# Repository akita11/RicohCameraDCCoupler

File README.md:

# Ricoh Camera DC Coupler

DC power supply coupler for Ricoh WG-10. Supply 7V or above to operate WG-10.

## Build

- fabricate PCB using "SMC-DCc10_gerber.zip" (original design using Eagle, PCB specs are shown in "SMC-DCc10_BOM.xlsx".), and divide into two sub-boards. (smaller one is outside WG-10 to attach external power cable, larger one is DC coupler attached in WG-10's battery area.)
- solder components listed in  "SMC-DCc10_BOM.xlsx".
- additional component: [FPC cable](https://www.digikey.jp/ja/products/detail/molex-llc/0151660079/3280961)

## Author

Junichi Akita (akita@ifdl.jp)

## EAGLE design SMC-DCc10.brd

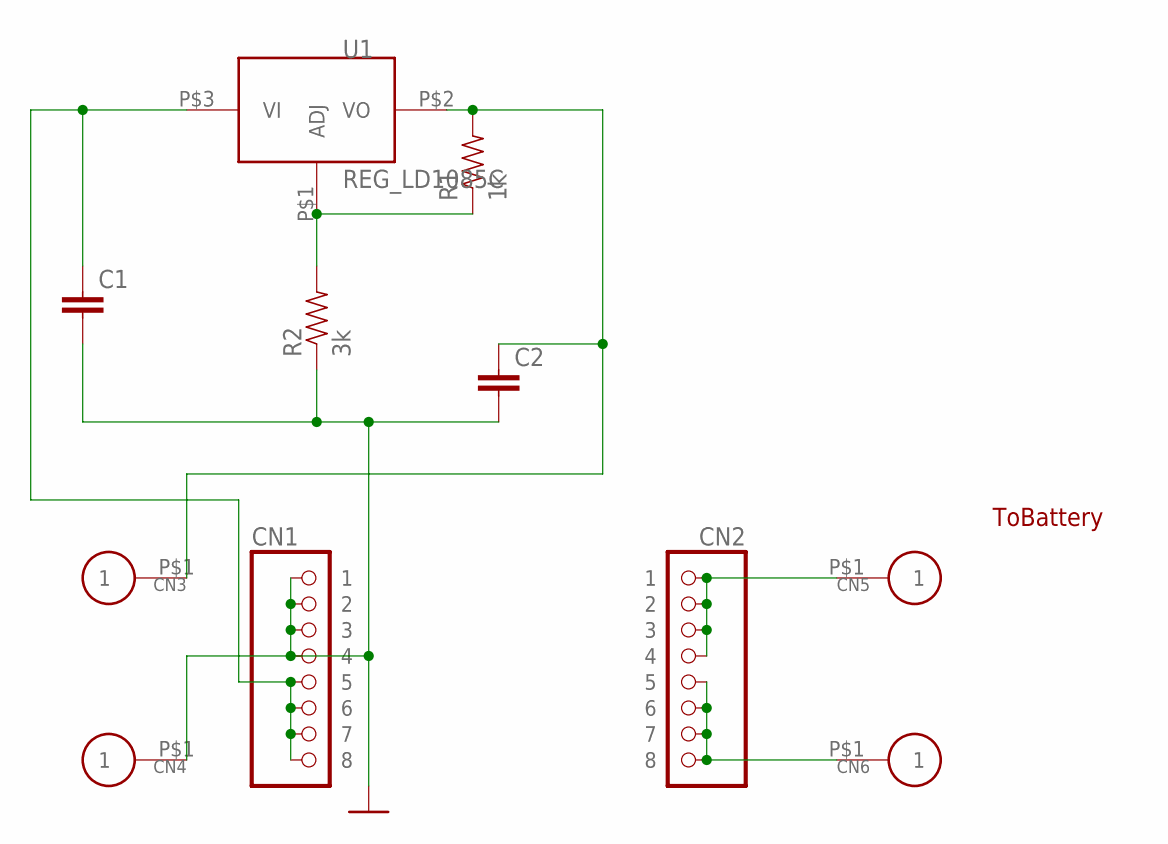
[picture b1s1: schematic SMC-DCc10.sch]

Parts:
C1: CAP0603; 0603
C2: CAP1206; 1206
CN1, CN2: CON_PINHD-1X8FPC05; CON_8P_FPC05MM
CN3, CN4, CN5, CN6: CON_P01SMD1MM; PAD_SMD1MM
R1: 1k; 0603
R2: 3k; 0603
U1: REG_LD1085C; TO-252-3

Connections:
GND: C1.2, C2.P$2 (2), CN1.P$1 (1), CN1.P$2 (2), CN1.P$3 (3), CN1.P$4 (4), CN4.P$1, R2.1
unnamed: CN2.P$5 (5), CN2.P$6 (6), CN2.P$7 (7), CN2.P$8 (8), CN6.P$1
unnamed: C2.P$1 (1), CN3.P$1, R1.2, U1.P$2 (VO)
unnamed: CN2.P$1 (1), CN2.P$2 (2), CN2.P$3 (3), CN2.P$4 (4), CN5.P$1
unnamed: R1.1, R2.2, U1.P$1 (ADJ)
unnamed: C1.1, CN1.P$5 (5), CN1.P$6 (6), CN1.P$7 (7), CN1.P$8 (8), U1.P$3 (VI)

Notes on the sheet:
ToBattery

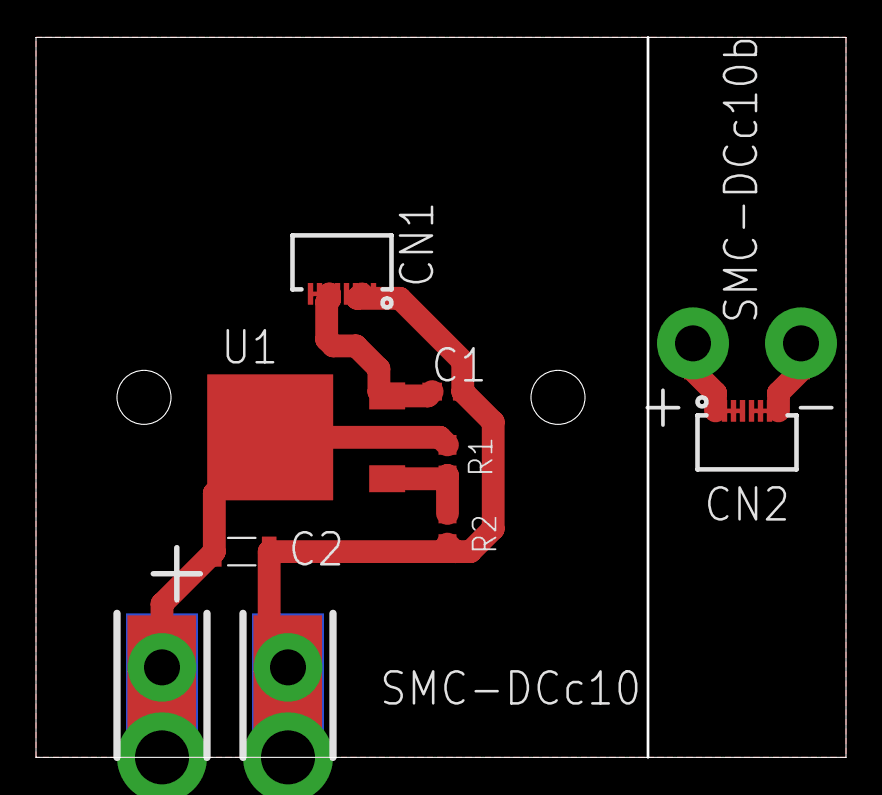
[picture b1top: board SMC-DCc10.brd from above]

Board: 2 copper layers, 45.0 x 40.0 mm, 11 parts (0 on the bottom side), 6 nets.

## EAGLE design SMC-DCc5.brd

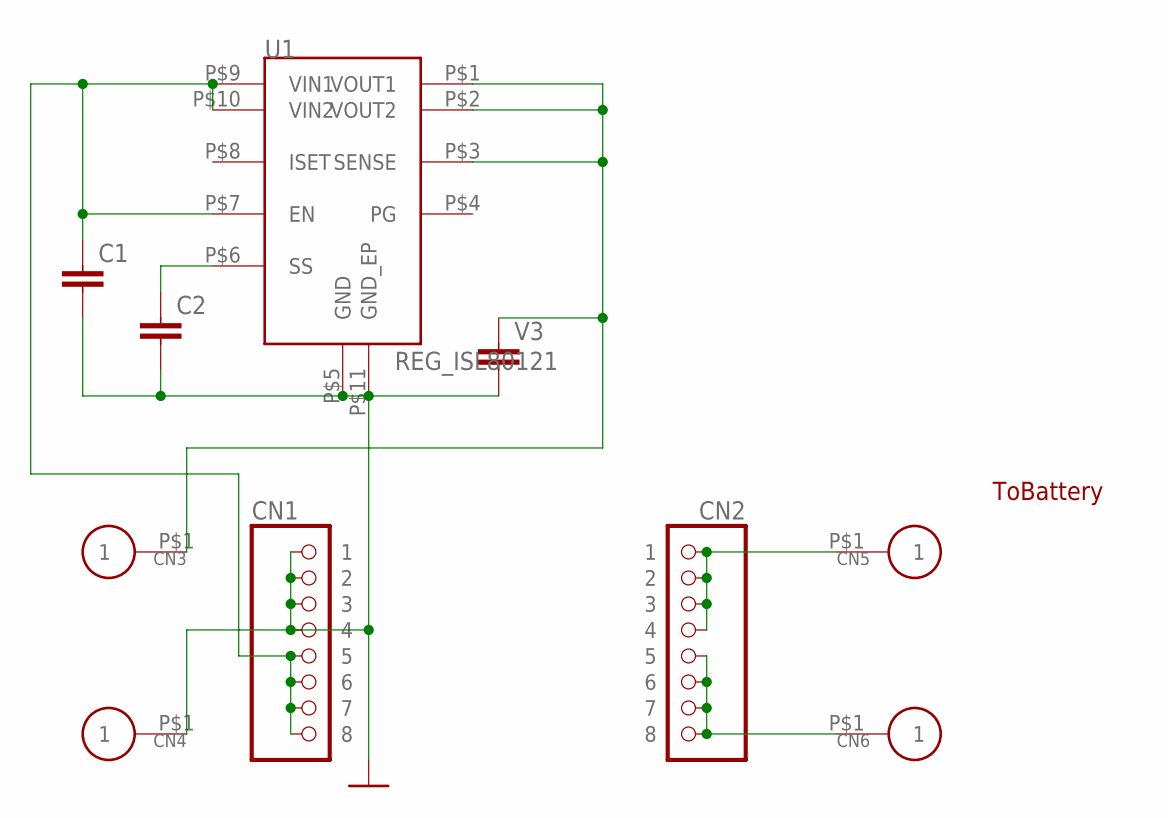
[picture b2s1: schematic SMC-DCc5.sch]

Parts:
C1, C2: CAP0603; 0603
CN1, CN2: CON_PINHD-1X8FPC05; CON_8P_FPC05MM
CN3, CN4, CN5, CN6: CON_P01SMD1MM; PAD_SMD1MM
U1: REG_ISL80121; DFN10_0.5MM
V3: CAP1206; 1206

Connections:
GND: C1.2, C2.2, CN1.P$1 (1), CN1.P$2 (2), CN1.P$3 (3), CN1.P$4 (4), CN4.P$1, U1.P$5 (GND), U1.P$11 (GND_EP), V3.P$2 (2)
unnamed: CN2.P$5 (5), CN2.P$6 (6), CN2.P$7 (7), CN2.P$8 (8), CN6.P$1
unnamed: C2.1, U1.P$6 (SS)
unnamed: CN2.P$1 (1), CN2.P$2 (2), CN2.P$3 (3), CN2.P$4 (4), CN5.P$1
P1: C1.1, CN1.P$5 (5), CN1.P$6 (6), CN1.P$7 (7), CN1.P$8 (8), U1.P$7 (EN), U1.P$9 (VIN1), U1.P$10 (VIN2)
P1O: CN3.P$1, U1.P$1 (VOUT1), U1.P$2 (VOUT2), U1.P$3 (SENSE), V3.P$1 (1)

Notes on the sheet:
ToBattery

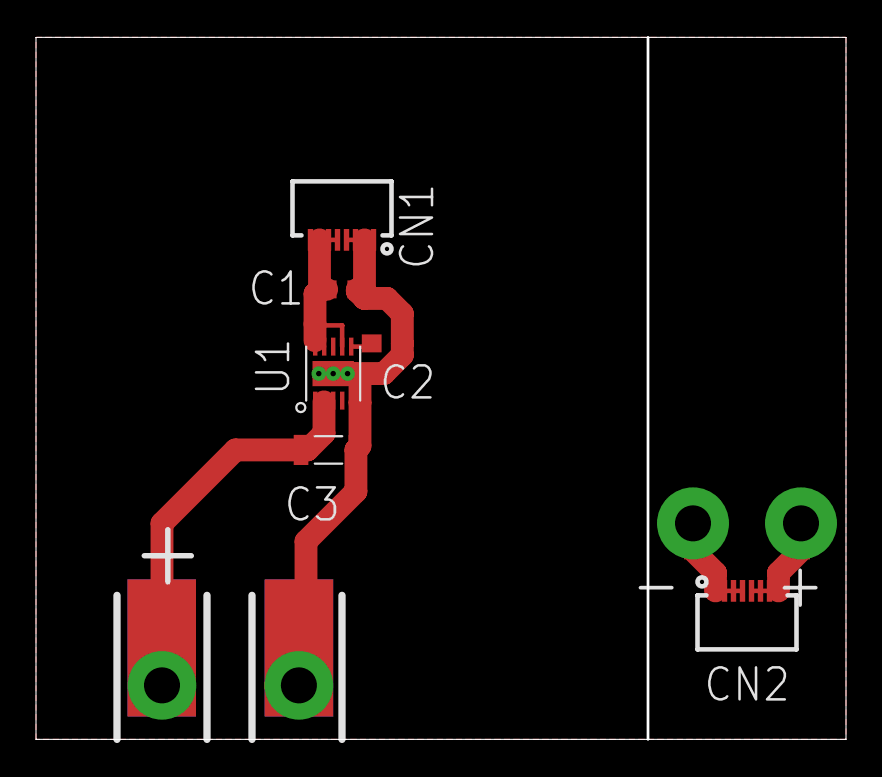
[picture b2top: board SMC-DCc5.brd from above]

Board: 2 copper layers, 45.0 x 39.0 mm, 10 parts (0 on the bottom side), 6 nets.

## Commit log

2022-09-06 add DCc10
2022-09-06 add spacer
2022-09-06 add README, photo
2022-09-06 rename README
2022-09-06 rename photo
